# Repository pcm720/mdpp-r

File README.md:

## MegaDrive++ R

**MegaDrive++ R** is a modchip for the **Sega Mega Drive/Genesis** heavily inspired by [MegaDrive++ project](https://github.com/SukkoPera/MegaDrivePlusPlus/).
It uses cheap ATmega88PA microcontroller, [cheap PCB](https://oshpark.com/shared_projects/NskgzQ7B) and supports following features:
- **Region switching**: allows user to switch regions with a button combination on Player 1 controller or Reset button.
  - Hold **Left + Start + A** for two seconds to change region to USA, **Left + Start + B** to change region to Europe, and **Left + Start + C** to change region to Japan.
  - Hold **Right** instead of **Left** to change region **and** reset the console.
  - Hold **Left + Start + A + B + C** to save current region to memory and use it as default every time you turn on your console.
  - Hold the **Reset** button for more than four seconds to cycle through modes. This will reset the console.
  - Button combos can be customized in common.h.
- **In-game Reset**: hold **Start + A + B + C** to reset the console.
- Dual-frequency oscillator support: PCB has a special pin for DFO control.
- Unlike [MegaDrive++](https://github.com/SukkoPera/MegaDrivePlusPlus/), it doesn't support reset level autosensing, so to use it on boards with active-high reset signal you'll need to comment out a line in common.h. Note that this is untested: I don't own any consoles with active-high reset.
- Suggested PCB layout is optimized for Model 2 VA1 board.

Visit [wiki](https://github.com/pcm720/mdpp-r/wiki) for installation diagram for Model 2 VA1 board.

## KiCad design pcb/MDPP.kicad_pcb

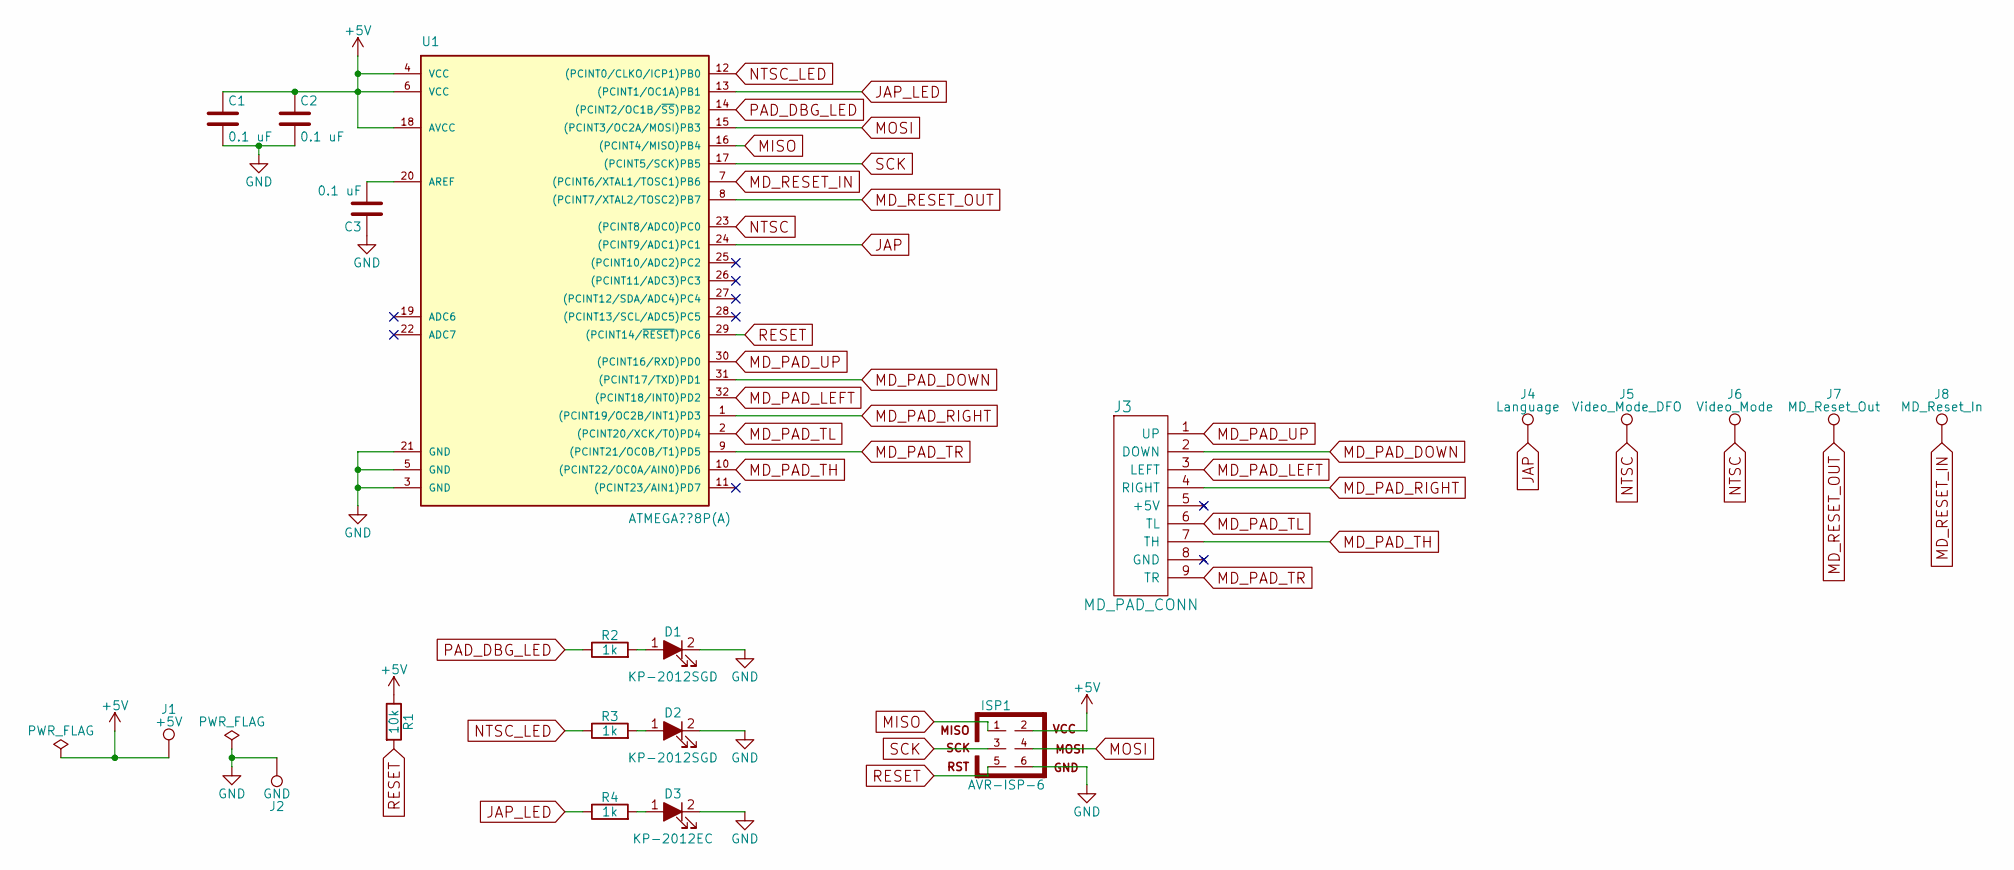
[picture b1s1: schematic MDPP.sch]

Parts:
D1, D2: KP-2012SGD
D3: KP-2012EC; KP-2012SGD
ISP1: AVR-ISP-6; AVR-ISP-6-SMD
J1: +5V; Soldering_Point_1.5x3mm
J2: GND; Soldering_Point_1.5x3mm
J3: MD_PAD_CONN
J4: Language; Soldering_Point_1.5x3mm
J5: Video_Mode_DFO; Soldering_Point_1.5x3mm
J6: Video_Mode; Soldering_Point_1.5x3mm
J7: MD_Reset_Out; Soldering_Point_1.5x3mm
J8: MD_Reset_In; Soldering_Point_1.5x3mm
R1: 10k; R_0805_HandSoldering
R2, R3, R4: 1k; C_0805
U1: ATMEGA??8P(A); TQFP-32_7x7mm_Pitch0.8mm
С1, С2, С3: 0.1 uF; C_0603_HandSoldering

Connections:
+5V: ISP1.2, J1.1, R1.1, U1.4 (VCC), U1.6 (VCC), U1.18 (AVCC), С1.1, С2.1
GND: D1.2 (A), D2.2 (A), D3.2 (A), ISP1.6, J2.1, U1.3 (GND), U1.5 (GND), U1.21 (GND), С1.2, С2.2, С3.1
JAP: J4.1, U1.24 ((PCINT9/ADC1)PC1)
JAP_LED: R4.1, U1.13 ((PCINT1/OC1A)PB1)
MD_PAD_DOWN: J3.2 (DOWN), U1.31 ((PCINT17/TXD)PD1)
MD_PAD_LEFT: J3.3 (LEFT), U1.32 ((PCINT18/INT0)PD2)
MD_PAD_RIGHT: J3.4 (RIGHT), U1.1 ((PCINT19/OC2B/INT1)PD3)
MD_PAD_TH: J3.7 (TH), U1.10 ((PCINT22/OC0A/AIN0)PD6)
MD_PAD_TL: J3.6 (TL), U1.2 ((PCINT20/XCK/T0)PD4)
MD_PAD_TR: J3.9 (TR), U1.9 ((PCINT21/OC0B/T1)PD5)
MD_PAD_UP: J3.1 (UP), U1.30 ((PCINT16/RXD)PD0)
MD_RESET_IN: J8.1, U1.7 ((PCINT6/XTAL1/TOSC1)PB6)
MD_RESET_OUT: J7.1, U1.8 ((PCINT7/XTAL2/TOSC2)PB7)
MISO: ISP1.1, U1.16 ((PCINT4/MISO)PB4)
MOSI: ISP1.4, U1.15 ((PCINT3/OC2A/MOSI)PB3)
NTSC: J5.1, J6.1, U1.23 ((PCINT8/ADC0)PC0)
NTSC_LED: R3.1, U1.12 ((PCINT0/CLKO/ICP1)PB0)
unnamed: D1.1 (K), R2.2
unnamed: D2.1 (K), R3.2
unnamed: D3.1 (K), R4.2
unnamed: U1.20 (AREF), С3.2
PAD_DBG_LED: R2.1, U1.14 ((PCINT2/OC1B/~SS~)PB2)
RESET: ISP1.5, R1.2, U1.29 ((PCINT14/~RESET~)PC6)
SCK: ISP1.3, U1.17 ((PCINT5/SCK)PB5)

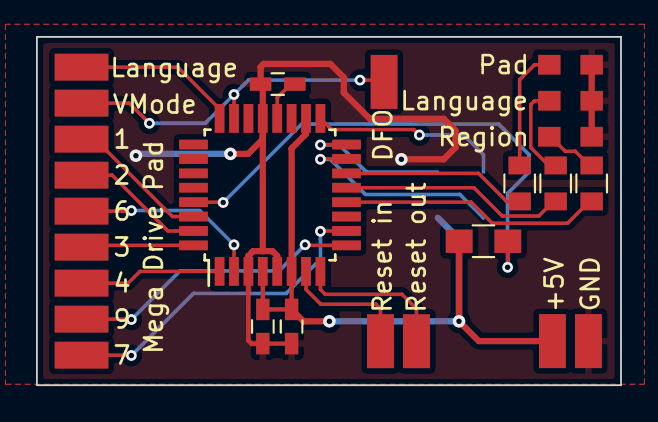
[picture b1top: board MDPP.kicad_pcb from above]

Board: 2 copper layers, 32.4 x 19.3 mm, 20 parts (1 on the bottom side), 24 nets.

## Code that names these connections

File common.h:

/*
Main definitions file for MegaDrive++ R
    Copyright (C) 2018-2019 pcm720 <pcm720@gmail.com>
    This program is free software: you can redistribute it and/or modify
    it under the terms of the GNU General Public License as published by
    the Free Software Foundation, either version 3 of the License, or
    (at your option) any later version.
    This program is distributed in the hope that it will be useful,
    but WITHOUT ANY WARRANTY; without even the implied warranty of
    MERCHANTABILITY or FITNESS FOR A PARTICULAR PURPOSE.  See the
    GNU General Public License for more details.
    You should have received a copy of the GNU General Public License
    along with this program.  If not, see 
<http://www.gnu.org/licenses/>.
*/

#ifndef COMMON_H_
#define COMMON_H_

#include <avr/io.h>
#include <util/delay.h>

// Undefine for Mega Drives with active high reset (VA5 and lower (?))
#define RESET_ACTIVE_LOW

// Amount of (seconds - 1) to monitor the combo for before switching the region or resetting the console
#define LENGTH_COMBO 1
// Amount of (seconds - 1) to monitor reset button for
#define LENGTH_RESET 2

// Pad button status map: S A C B R L D U, button is 0 if pressed
#define COMBO_RESET       0x0F // Start + A + B + C          / ~(11110000)
#define COMBO_SAVE        0x0B // Left + Start + A + B + C   / ~(11110100) | Saves current region to EEPROM
#define COMBO_USA         0x3B // Left + Start + A           / ~(11000100)
#define COMBO_EUR         0x6B // Left + Start + B           / ~(10010100)
#define COMBO_JAP         0x5B // Left + Start + C           / ~(10100100)
#define COMBO_USA_RESET   0x37 // Right + Start + A          / ~(11001000)
#define COMBO_EUR_RESET   0x67 // Right + Start + B          / ~(10011000)
#define COMBO_JAP_RESET   0x57 // Right + Start + C          / ~(10101000)
#define COMBO_OFF         0x00 // To use when no combo is currently active, don't change this

// Pins:    LANGUAGE    VIDEOMODE
// USA:     HIGH        HIGH
// EUR:     HIGH        LOW
// JAP:     LOW         HIGH
#define JAP 0x1 // 01
#define EUR 0x2 // 10
#define USA 0x3 // 11
#define NXT 0x4 // Next region
#define DEFAULT_REGION USA // Default region to use if EEPROM read fails or if this is first boot

// End of configurable area

#ifdef RESET_ACTIVE_LOW
    #define PINB_RESET ~PINB
#else
    #define PINB_RESET PINB
#endif

#endif

/* 
 * Pin assignments:
 * PORT B:
 * PORTB Map: 76XXX210
 * NTSC_LED         PB0 (OUT)
 * JAP_LED          PB1 (OUT)
 * PAD_DBG_LED      PB2 (OUT)
 * MD_RESET_IN      PB6 (IN) [UNUSED]
 * MD_RESET_OUT     PB7 (IN/OUT)
 * 
 * PORT C:
 * PORTC Map: XXXXXX10
 * NTSC     PC0 (OUT)
 * JAP      PC1 (OUT)
 * 
 * PORT D:
 * PORTD Map: X6543210 / All are inputs except PD7
 * MD_PAD_UP        PD0 (Pad Pin 1 / UP)
 * MD_PAD_DOWN      PD1 (Pad Pin 2 / DOWN)
 * MD_PAD_LEFT      PD2 (Pad Pin 3 / LEFT)
 * MD_PAD_RIGHT     PD3 (Pad Pin 4 / RIGHT)
 * MD_PAD_TL        PD4 (Pad Pin 6 / A/B)
 * MD_PAD_TR        PD5 (Pad Pin 9 / Start/C)
 * MD_PAD_TH        PD6 (Pad Pin 7 / SELECT)
 * 
 * Some technical notes on Mega Drive gamepads:
 *
 * 3-button pad:
 * State   Select(TH)   Up    Down    Left    Right    TL    TR
 * 0       HIGH         Up    Down    Left    Right    B     C
 * 1       LOW          Up    Down    LOW     LOW      A     Start
 * 
 * 6-button pad:
 * State   Select(TH)   Up    Down    Left    Right    TL    TR
 * 0       HIGH         Up    Down    Left    Right    B     C
 * 1       LOW          Up    Down    LOW     LOW      A     Start
 * 2       HIGH         Up    Down    Left    Right    B     C
 * 3       LOW          Up    Down    LOW     LOW      A     Start
 * 4       HIGH         Up    Down    Left    Right    B     C
 * 5       LOW          LOW   LOW     LOW     LOW      A     Start
 * 6       HIGH         Z     X       Y       Mode     B     C
 * 7       LOW          -     -       -       -        A     Start
 * 
 * Notes:
 * 1. Select idles in HIGH state in official games
 *    Unlicensed stuff like Everdrive and chinese multicarts actually read pads incorrectly, leaving Select pulled down after reading.
 *    We need to consider every option.
 * 2. For 3-button mode, Select pulse length is 6-6.5 us;
 *    For 6-button mode, Select period (Tsel) is non-uniform and depends on the game.
 *      For Street Fighter 2, select cycle looks like this:
 *          Select is active high
 *          first select pluse (to LOW state) is 25 us
 *          second (HIGH) is 4.7-5 us
 *          third (LOW) is 8-9 us
 *          fourth (HIGH) is 4.7-5 us
 *          fifth (LOW) is 9-11 us
 *          sixth (HIGH) is 4.7-5 us
 *          seventh (LOW) is 25 us
 *      For Streets of Rage 3:  
 *          Select is active high
 *          first select pluse (to LOW state) is 10 us
 *          second (HIGH) is 6.2 us
 *          third (LOW) is 7.3 us
 *          fourth (HIGH) is 6.25 us
 *          fifth (LOW) is 7.3 us
 *          sixth (HIGH) is 6.25 us
 *          seventh (LOW) is 7 us
 * 3. 6-button Select cycle length is around 50-100 us (50 for Streets of Rage 3, 84 for Street Fighter 2)
 * 4. Pad internal reset (Tres) is 2 ms (according to SEGA specifications on 6-button pad)
 * 5. Some 3-button pad-only games pulse Select line multiple times in 2 ms interval, triggering 6-button pad to output more than two states.
 *    For example, Ms. Pac-Man pulses Select line thrice in 100 us interval. This behaviour is considered incorrect.
 *    We can skip these pulses by delaying for more than 100 us after the first level change.
 * 6. It takes ~200-600 ns for 6-button pad to update its output after Select level change
 * 7. Frame period is 16.67 ms for NTSC and 20 ms for PAL
 * 8. Since we don't really need to read all buttons of 6-button pad, we can pretend that it doesn't exist
 */

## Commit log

2019-01-21 Added PCB design
2019-01-24 Added README
